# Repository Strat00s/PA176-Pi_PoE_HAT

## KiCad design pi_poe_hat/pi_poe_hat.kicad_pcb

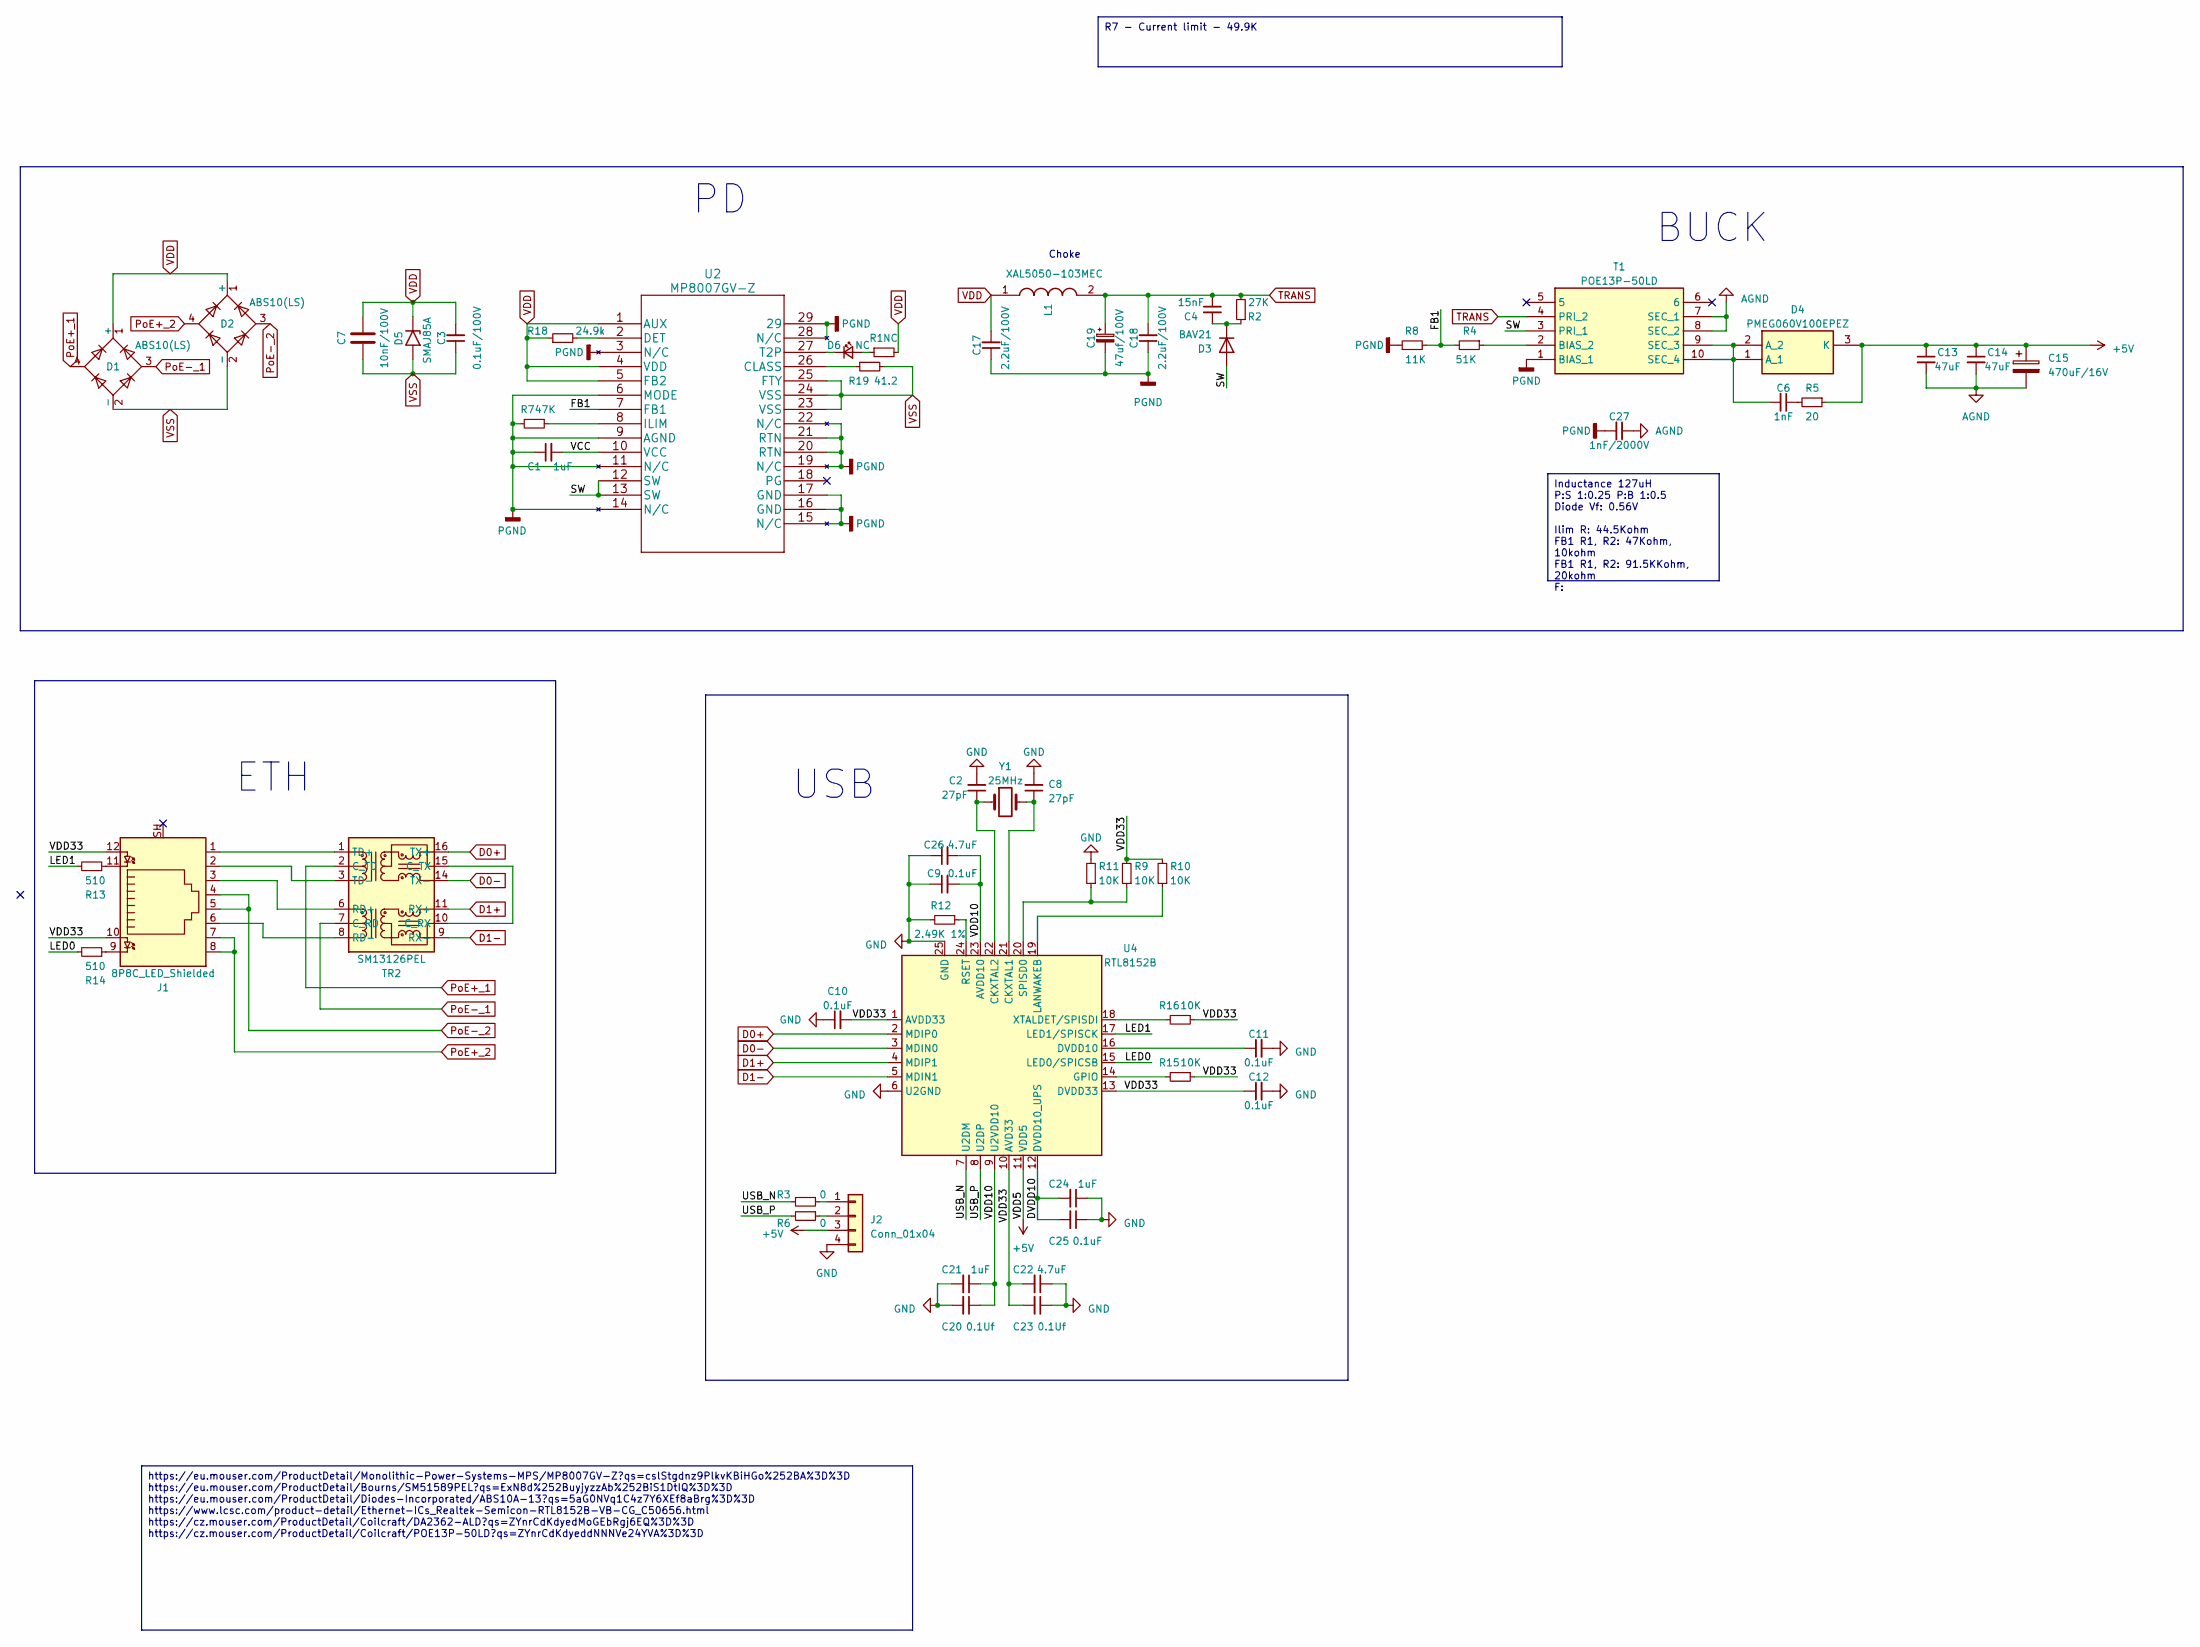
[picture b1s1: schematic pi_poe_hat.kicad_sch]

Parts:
C1, C21, C24: 1uF; C_0603_1608Metric_Pad1.08x0.95mm_HandSolder
C2, C8: 27pF; C_0603_1608Metric_Pad1.08x0.95mm_HandSolder
C3: 0.1uF/100V; C_1206_3216Metric_Pad1.33x1.80mm_HandSolder
C4: 15nF; C_0805_2012Metric_Pad1.18x1.45mm_HandSolder
C6: 1nF; C_0603_1608Metric_Pad1.08x0.95mm_HandSolder
C7: 10nF/100V; C_0805_2012Metric_Pad1.18x1.45mm_HandSolder
C9, C10, C11, C12, C25: 0.1uF; C_0603_1608Metric_Pad1.08x0.95mm_HandSolder
C13, C14: 47uF; C_1210_3225Metric_Pad1.33x2.70mm_HandSolder
C15: 470uF/16V; CP_Radial_D10.0mm_P5.00mm
C17, C18: 2.2uF/100V; C_1210_3225Metric_Pad1.33x2.70mm_HandSolder
C19: 47uf/100V; CP_Radial_D8.0mm_P3.50mm
C20, C23: 0.1Uf; C_0603_1608Metric_Pad1.08x0.95mm_HandSolder
C22, C26: 4.7uF; C_0805_2012Metric_Pad1.18x1.45mm_HandSolder
C27: 1nF/2000V; C_1812_4532Metric_Pad1.57x3.40mm_HandSolder
D1, D2: ABS10(LS); Diode_Bridge_Diotec_ABS
D3: BAV21; D_SOD-123
D4: PMEG060V100EPEZ; Manufacturer_Part_Number PMEG060V100EPEZ
D5: SMAJ85A; D_SMA
D6: NC; LED_0603_1608Metric_Pad1.05x0.95mm_HandSolder
J1: 8P8C_LED_Shielded; RJ45_Amphenol_RJHSE538X
J2: Conn_01x04; PinHeader_1x04_P2.54mm_Vertical
L1: XAL5050-103MEC; L_Coilcraft_XAL5050-XXX; Manufacturer_Part_Number XAL5050-103MEC; Mouser Part Number 994-XAL5050-103MEC
R1: NC; R_0603_1608Metric_Pad0.98x0.95mm_HandSolder
R2: 27K; R_1206_3216Metric_Pad1.30x1.75mm_HandSolder
R3, R6: 0; R_0603_1608Metric_Pad0.98x0.95mm_HandSolder
R4: 51K; R_0603_1608Metric_Pad0.98x0.95mm_HandSolder
R5: 20; R_0805_2012Metric_Pad1.20x1.40mm_HandSolder
R7: 47K; R_0603_1608Metric_Pad0.98x0.95mm_HandSolder
R8: 11K; R_0603_1608Metric_Pad0.98x0.95mm_HandSolder
R9, R10, R11, R15, R16: 10K; R_0603_1608Metric_Pad0.98x0.95mm_HandSolder
R12: 2.49K 1%; R_0603_1608Metric_Pad0.98x0.95mm_HandSolder
R13, R14: 510; R_0603_1608Metric_Pad0.98x0.95mm_HandSolder
R18: 24.9k; R_0603_1608Metric_Pad0.98x0.95mm_HandSolder
R19: 41.2; R_0603_1608Metric_Pad0.98x0.95mm_HandSolder
T1: POE13P-50LD; POE13P50LD; Mouser Part Number 994-POE13P-50LD
TR2: SM13126PEL; Transformer_Ethernet_Bourns_PT61017PEL
U2: MP8007GV-Z
U4: RTL8152B; QFN-24-1EP_4x4mm_P0.5mm_EP2.6x2.6mm
Y1: 25MHz; ABLS

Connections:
+5V: C13.1, C14.1, C15.1, D4.3 (K), J2.3, R5.1, U4.11 (VDD5)
/DVDD10: C24.2, C25.2, U4.12 (DVDD10_UPS)
/FB1: R4.2, R8.2, U2.7 (FB1)
/LED0: R14.2, U4.15 (LED0/SPICSB)
/LED1: R13.2, U4.17 (LED1/SPISCK)
/SW: D3.2 (A), T1.3 (PRI_1), U2.12 (SW), U2.13 (SW)
/USB_N: R3.2, U4.7 (U2DM)
/USB_P: R6.2, U4.8 (U2DP)
/VCC: C1.2, U2.10 (VCC)
/VDD10: C9.2, C20.1, C21.1, C26.2, U4.9 (U2VDD10), U4.23 (AVDD10)
/VDD33: C10.2, C12.1, C22.2, C23.2, J1.10, J1.12, R9.2, R10.2, R15.1, R16.1, U4.1 (AVDD33), U4.10 (AVD33), U4.13 (DVDD33)
D0+: TR2.16 (TX+), U4.2 (MDIP0)
D0-: TR2.14 (TX-), U4.3 (MDIN0)
D1+: TR2.11 (RX+), U4.4 (MDIP1)
D1-: TR2.9 (RX-), U4.5 (MDIN1)
GNDD: C1.1, C17.1, C18.1, C19.2, C27.2, R7.2, R8.1, T1.1 (BIAS_1), U2.3 (N/C), U2.6 (MODE), U2.9 (AGND), U2.11 (N/C), U2.14 (N/C), U2.15 (N/C), U2.16 (GND), U2.17 (GND), U2.19 (N/C), U2.20 (RTN), U2.21 (RTN), U2.22 (N/C), U2.28 (N/C), U2.29
unnamed: C6.1, R5.2
unnamed: C4.2, D3.1 (K), R2.1
unnamed: C6.2, D4.1 (A_1), D4.2 (A_2), T1.9 (SEC_3), T1.10 (SEC_4)
unnamed: D6.2 (A), R1.1
unnamed: D6.1 (K), U2.27 (T2P)
unnamed: J1.9, R14.1
unnamed: J1.11, R13.1
unnamed: J2.1, R3.1
unnamed: J2.2, R6.1
unnamed: R4.1, T1.2 (BIAS_2)
unnamed: TR2.10 (C_RX), TR2.15 (C_TX)
unnamed: J1.3, TR2.6 (RD+)
unnamed: J1.6, TR2.8 (RD-)
unnamed: J1.1, TR2.1 (TD+)
unnamed: J1.2, TR2.3 (TD-)
unnamed: R19.1, U2.26 (CLASS)
unnamed: R18.2, U2.2 (DET)
unnamed: R7.1, U2.8 (ILIM)
unnamed: C8.1, U4.21 (CKXTAL1), Y1.2
unnamed: C2.1, U4.22 (CKXTAL2), Y1.1
unnamed: C11.1, U4.16 (DVDD10)
unnamed: R15.2, U4.14 (GPIO)
unnamed: R10.1, U4.19 (LANWAKEB)
unnamed: R12.1, U4.24 (RSET)
unnamed: R9.1, R11.1, U4.20 (SPISD0)
unnamed: R16.2, U4.18 (XTALDET/SPISDI)
PoE+_1: D1.4, TR2.2 (C_TD)
PoE+_2: D2.4, J1.7, J1.8
PoE-_1: D1.3, TR2.7 (C_RD)
PoE-_2: D2.3, J1.4, J1.5
TRANS: C4.1, C18.2, C19.1, L1.2, R2.2, T1.4 (PRI_2), T1.5
VDD: C3.2, C7.2, C17.2, D1.1 (+), D2.1 (+), D5.1 (A1), L1.1, R1.2, R18.1, U2.1 (AUX), U2.4 (VDD), U2.5 (FB2)
VSS: C3.1, C7.1, D1.2 (-), D2.2 (-), D5.2 (A2), R19.2, U2.23 (VSS), U2.24 (VSS), U2.25 (FTY)

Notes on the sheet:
R7 - Current limit - 49.9K
Inductance 127uH P:S 1:0.25 P:B 1:0.5 Diode Vf: 0.56V Ilim R: 44.5Kohm FB1 R1, R2: 47Kohm, 10kohm FB1 R1, R2: 91.5KKohm, 20kohm F:
https://eu.mouser.com/ProductDetail/Monolithic-Power-Systems-MPS/MP8007GV-Z?qs=cslStgdnz9PlkvKBiHGo%252BA%3D%3D https://eu.mouser.com/ProductDetail/Bourns/SM51589PEL?qs=ExN8d%252BuyjyzzAb%252BiS1DtIQ%3D%3D https://eu.mouser.com/ProductDetail/Diodes-Incorporated/ABS10A-13?qs=5aG0NVq1C4z7Y6XEf8aBrg%3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
Choke
BUCK
USB
ETH

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
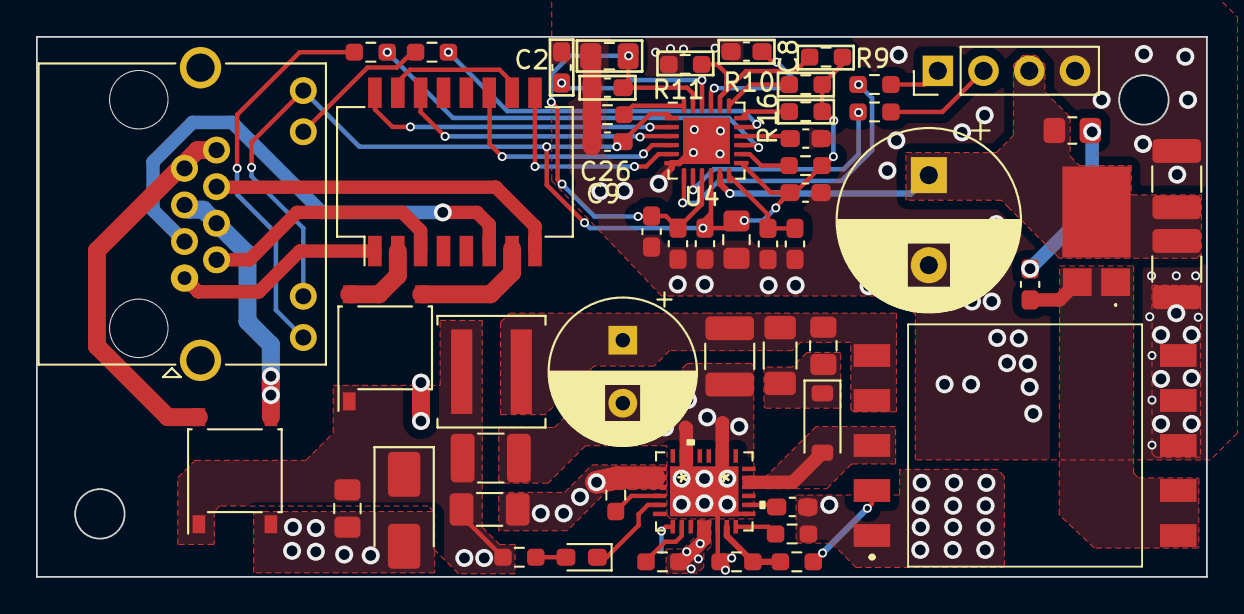
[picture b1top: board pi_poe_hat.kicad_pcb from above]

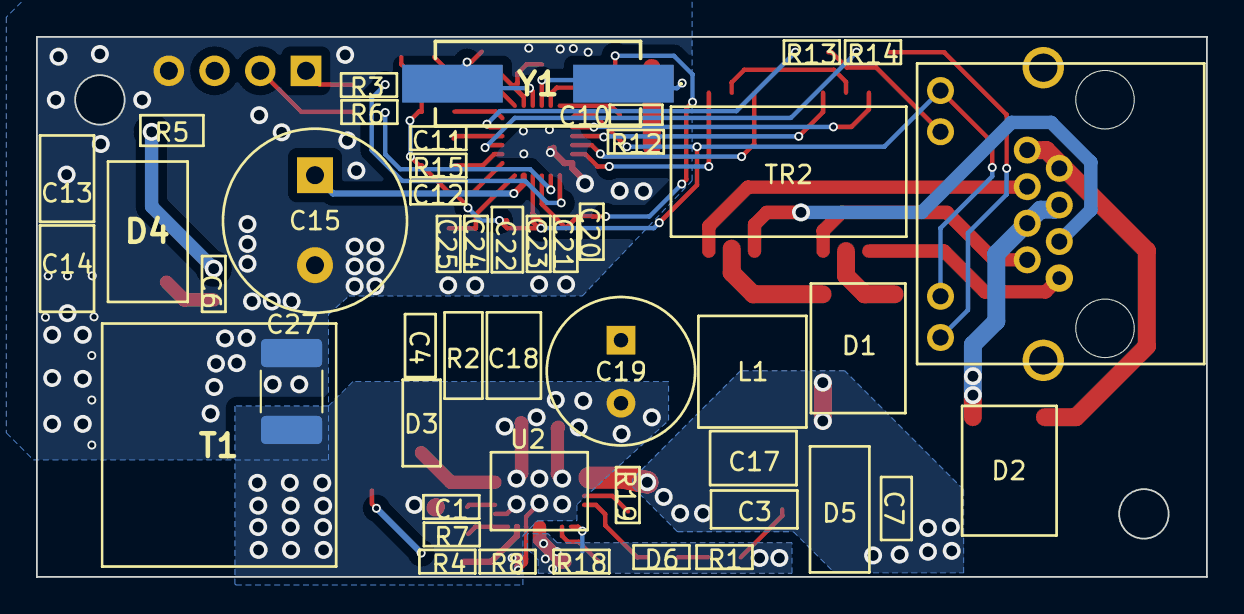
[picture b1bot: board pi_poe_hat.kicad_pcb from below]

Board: 2 copper layers, 65.0 x 30.0 mm, 57 parts (2 on the bottom side), 50 nets.

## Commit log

2023-03-05 obsidia vault
2023-03-07 pcb start
2023-03-09 PD done???
2023-03-09 new PDs
2023-03-09 PD final
2023-03-09 nothing
2023-03-14 almost done
2023-03-14 pdfs
2023-03-15 done?
2023-03-23 pcb continue
2023-03-24 ttgo poe reference
2023-04-04 pcb footprint done
2023-04-04 v 1.0 of pcb almost done
2023-04-06 second pcb almost done
2023-04-06 pcb almost done
2023-04-06 second pcb done
2023-04-07 pcb done
2023-05-16 new possible fix img

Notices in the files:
parts and their libraries:
Copyright 2021 Accelerated Designs. All rights reserved.
